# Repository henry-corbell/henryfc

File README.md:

# henryfc

server for tracking changes and updates for the HenryFC flight controller

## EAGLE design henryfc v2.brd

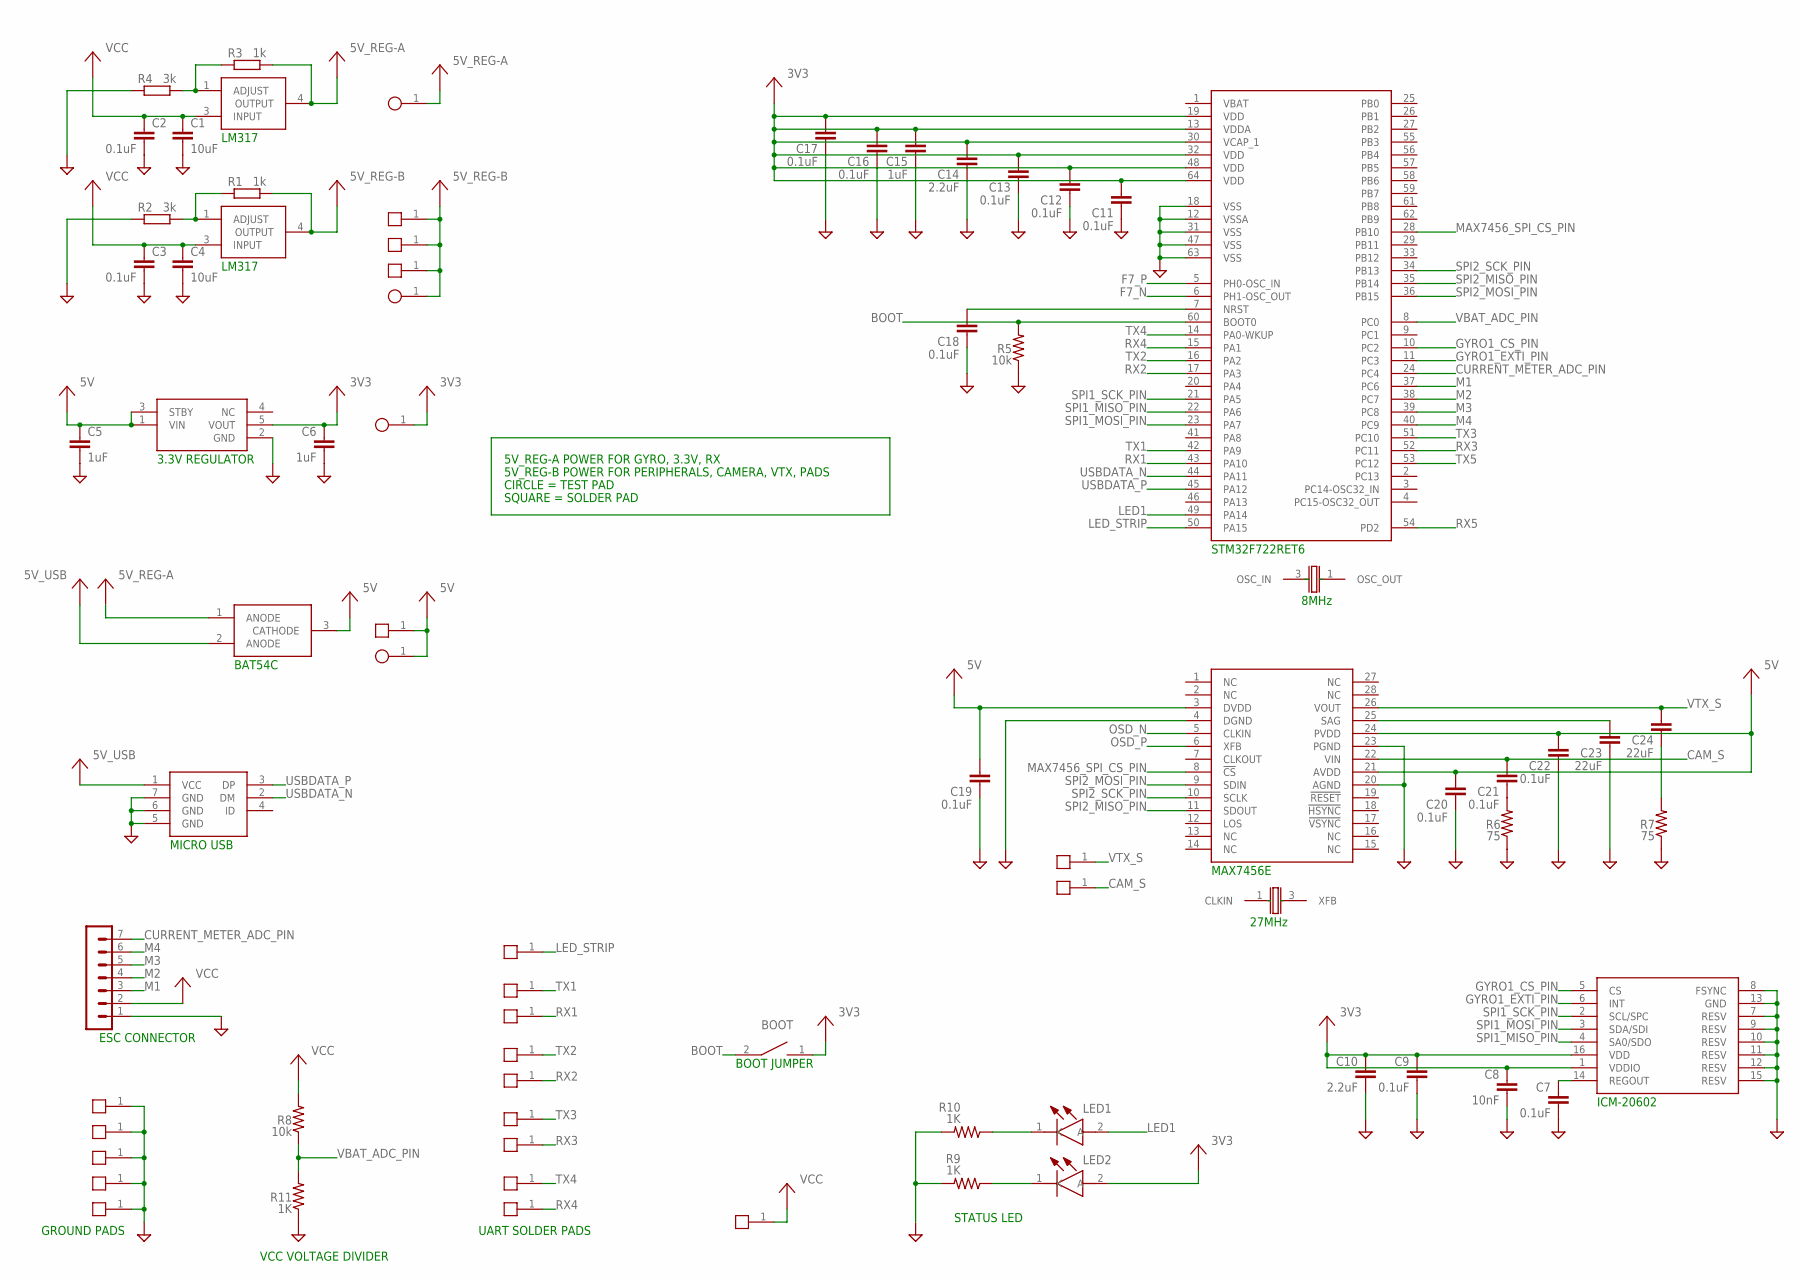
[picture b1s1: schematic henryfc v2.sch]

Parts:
C1, C4: 10uF; C0603
C2, C3: 0.1uF; C0603
C5, C6: 1uF; C0603
C7, C9, C11, C12, C13, C16, C17, C18, C19, C20, C21, C22: 0.1uF; C0402
C8: 10nF; C0402
C10, C14: 2.2uF; C0402
C15: 1uF; C0402
C23, C24: 22uF; C0402
LED1: KB_DELPS2.12-QHRI-24-Z555-10-S; KBDELPS212QHRI24Z55510S
LED2: KR_DELPS1.22-UHVI-26-H3Q4; KRDELPS122UHVI26H3Q4
R1, R3: 1k; R0603
R2, R4: 3k; R0603
R5, R8: 10k; R0402
R6, R7: 75; R0402
R9, R10, R11: 1K; R0402
TP1, TP2, TP3, TP4: TESTPOINT
U$1: BAT54C; SOT-23
U$2: BUXXSD5WG-3.3V-LDO; SSOP5
U$3, U$4: LM317DCYR; SOT-223
U$5: STM32F722; LQFP64
U$6: MICRO-USB
U$7: MAX7456; SSOP28
U$8: ICM-20602; LGA16-3X3
U$9: ECX-32-8MHZ; ECX-32-XTAL
U$10: NX3225GA-27MHZ; 3.2X2.5-XTAL
U$11: BOOT_JUMPER
U$13, U$14, U$15, U$19, U$20, U$21, U$22, U$23, U$24, U$25, U$26, U$27, U$28, U$29, U$30, U$31, U$32, U$33, U$34, U$35, U$36: SOLDERPAD
X1: SM07B-SRSS-TB

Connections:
3V3: C6.1, C8.1, C9.1, C10.1, C11.1, C12.1, C13.1, C14.1, C15.1, C16.1, C17.1, LED2.2 (A), TP2.1, U$2.5 (VOUT), U$5.13 (VDDA), U$5.19 (VDD), U$5.30 (VCAP_1), U$5.32 (VDD), U$5.48 (VDD), U$5.64 (VDD), U$8.1 (VDDIO), U$8.16 (VDD), U$11.1 ()
5V: C5.1, C19.1, C20.1, C22.1, TP1.1, U$1.3 (CATHODE), U$2.1 (VIN), U$2.3 (STBY), U$7.3 (DVDD), U$7.21 (AVDD), U$7.24 (PVDD), U$15.1
5V_REG-A: R3.2, TP4.1, U$1.1 (ANODE), U$4.4 (OUTPUT)
5V_REG-B: R1.2, TP3.1, U$3.4 (OUTPUT), U$13.1, U$14.1, U$25.1
5V_USB: U$1.2 (ANODE), U$6.1 (VCC)
BOOT: R5.2, U$5.60 (BOOT0), U$11.2 ()
CAM_S: C21.1, U$7.22 (VIN), U$31.1
CURRENT_METER_ADC_PIN: U$5.24 (PC4), X1.7
F7_N: U$5.6 (PH1-OSC_OUT), U$9.1 (OSC_OUT)
F7_P: U$5.5 (PH0-OSC_IN), U$9.3 (OSC_IN)
GND: C1.2, C2.2, C3.2, C4.2, C5.2, C6.2, C7.2, C8.2, C9.2, C10.2, C11.2, C12.2, C13.2, C14.2, C15.2, C16.2, C17.2, C18.2, C19.2, C20.2, C22.2, C23.2, R2.1, R4.1, R5.1, R6.1, R7.1, R9.2, R10.2, R11.1, U$2.2 (GND), U$5.12 (VSSA), U$5.18 (VSS), U$5.31 (VSS), U$5.47 (VSS), U$5.63 (VSS), U$6.5 (GND), U$6.6 (GND), U$6.7 (GND), U$7.4 (DGND), U$7.20 (AGND), U$7.23 (PGND), U$8.7 (RESV), U$8.8 (FSYNC), U$8.9 (RESV), U$8.10 (RESV), U$8.11 (RESV), U$8.12 (RESV), U$8.13 (GND), U$8.15 (RESV), U$19.1, U$20.1, U$21.1, U$27.1, U$35.1, X1.1
GYRO1_CS_PIN: U$5.10 (PC2), U$8.5 (CS)
GYRO1_EXTI_PIN: U$5.11 (PC3), U$8.6 (INT)
LED1: LED1.2 (A), U$5.49 (PA14)
LED_STRIP: U$5.50 (PA15), U$23.1
M1: U$5.37 (PC6), X1.3
M2: U$5.38 (PC7), X1.4
M3: U$5.39 (PC8), X1.5
M4: U$5.40 (PC9), X1.6
MAX7456_SPI_CS_PIN: U$5.28 (PB10), U$7.8 (!CS)
unnamed: R1.1, R2.2, U$3.1 (ADJUST)
unnamed: R3.1, R4.2, U$4.1 (ADJUST)
unnamed: C18.1, U$5.7 (NRST)
unnamed: C23.1, U$7.25 (SAG)
unnamed: C21.2, R6.2
unnamed: C7.1, U$8.14 (REGOUT)
unnamed: C24.2, R7.2
unnamed: LED1.1 (K), R10.1
unnamed: LED2.1 (K), R9.1
OSD_N: U$7.5 (CLKIN), U$10.1 (CLKIN)
OSD_P: U$7.6 (XFB), U$10.3 (XFB)
RX1: U$5.43 (PA10), U$34.1
RX2: U$5.17 (PA3), U$24.1
RX3: U$5.52 (PC11), U$28.1
RX4: U$5.15 (PA1), U$32.1
RX5: U$5.54 (PD2)
SPI1_MISO_PIN: U$5.22 (PA6), U$8.4 (SA0/SDO)
SPI1_MOSI_PIN: U$5.23 (PA7), U$8.3 (SDA/SDI)
SPI1_SCK_PIN: U$5.21 (PA5), U$8.2 (SCL/SPC)
SPI2_MISO_PIN: U$5.35 (PB14), U$7.11 (SDOUT)
SPI2_MOSI_PIN: U$5.36 (PB15), U$7.9 (SDIN)
SPI2_SCK_PIN: U$5.34 (PB13), U$7.10 (SCLK)
TX1: U$5.42 (PA9), U$36.1
TX2: U$5.16 (PA2), U$22.1
TX3: U$5.51 (PC10), U$26.1
TX4: U$5.14 (PA0-WKUP), U$30.1
TX5: U$5.53 (PC12)
USBDATA_N: U$5.44 (PA11), U$6.2 (DM)
USBDATA_P: U$5.45 (PA12), U$6.3 (DP)
VBAT_ADC_PIN: R8.1, R11.2, U$5.8 (PC0)
VCC: C1.1, C2.1, C3.1, C4.1, R8.2, U$3.3 (INPUT), U$4.3 (INPUT), U$33.1, X1.2
VTX_S: C24.1, U$7.26 (VOUT), U$29.1

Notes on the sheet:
8MHz
ICM-20602
LM317
3.3V REGULATOR
BAT54C
MICRO USB
STM32F722RET6
27MHz
MAX7456E
ESC CONNECTOR
GROUND PADS
VCC VOLTAGE DIVIDER
UART SOLDER PADS
BOOT JUMPER
STATUS LED
5V_REG-A POWER FOR GYRO, 3.3V, RX
5V_REG-B POWER FOR PERIPHERALS, CAMERA, VTX, PADS
CIRCLE = TEST PAD
SQUARE = SOLDER PAD

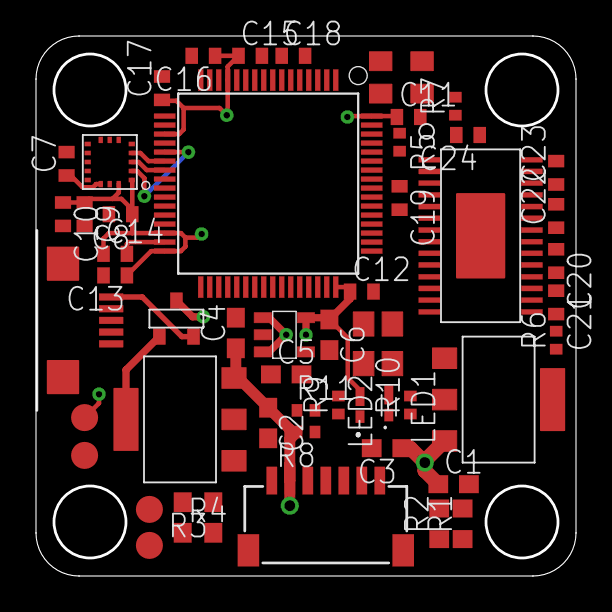
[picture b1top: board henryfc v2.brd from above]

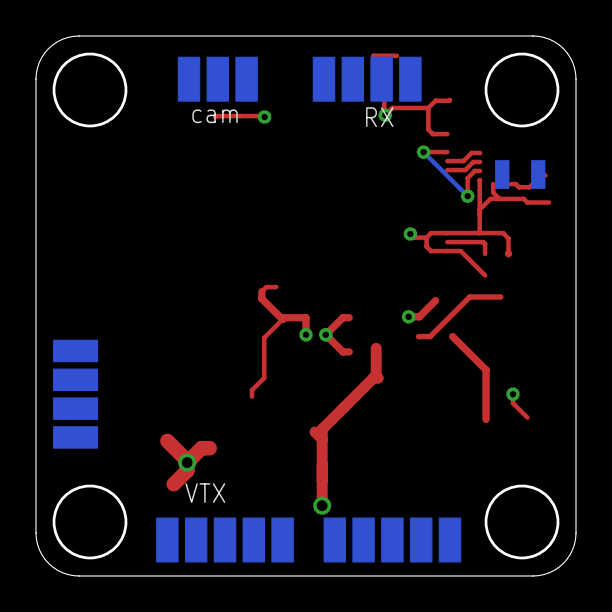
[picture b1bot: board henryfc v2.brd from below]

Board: 4 copper layers, 29.8 x 29.8 mm, 74 parts (22 on the bottom side), 50 nets.

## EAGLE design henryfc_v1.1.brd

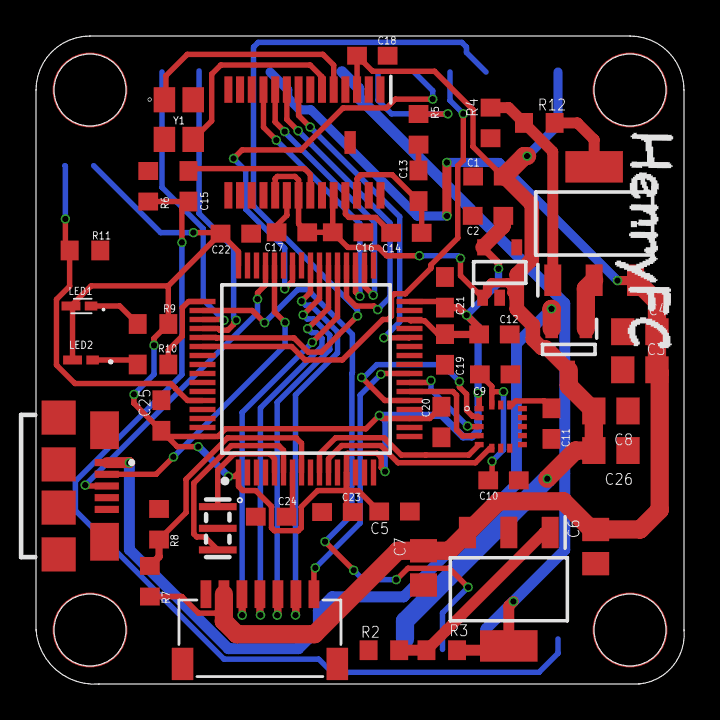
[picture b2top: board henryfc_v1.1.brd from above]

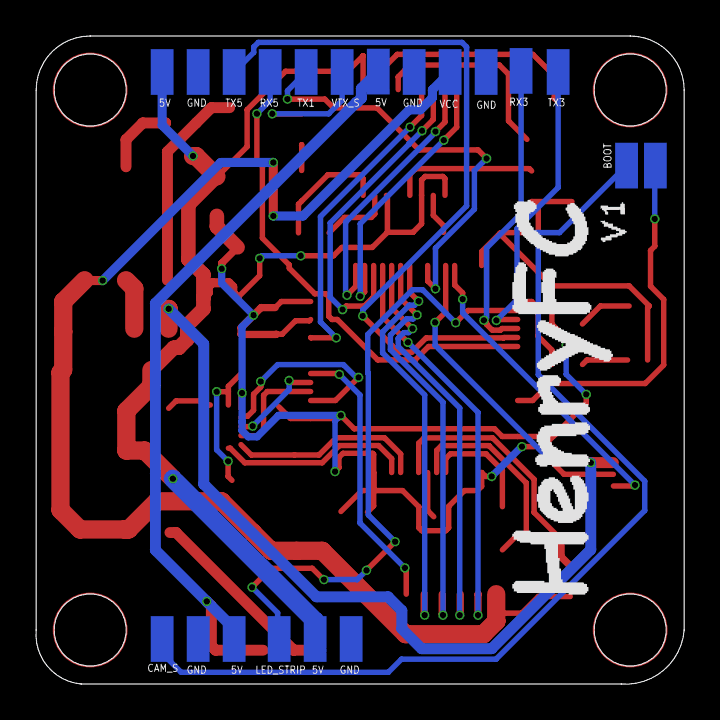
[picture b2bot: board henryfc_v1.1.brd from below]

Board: 2 copper layers, 36.0 x 36.0 mm, 70 parts (20 on the bottom side), 49 nets.

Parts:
C1, C2, C5: 1uF; C0603
C3, C6, C8: 0.1uF; C0805
C4, C7, C26: 10uF; C0805
C9, C11, C15, C16, C17, C18, C20, C21, C22, C23, C24, C25: 0.1uF; C0603
C10, C19: 2.2uF; C0603
C12: 10nF; C0603
C13, C14: 22uF; C0603
D1: BAT54C; SOT95P240X120-3N
IC1, IC5: LM317DCYR; SOT230P700X180-4N
IC2: ICM-20602; PULL-BACK-QFN-16
IC3: AT7456E; SOP65P640X120-29N
IC4: STM32F722RET6TR; QFP50P1200X1200X160-64N
J2: 10118192-0001LF; 101181920001LF
LED1: KB_DELPS2.12-QHRI-24-Z555-10-S; KBDELPS212QHRI24Z55510S
LED2: KR_DELPS1.22-UHVI-26-H3Q4; KRDELPS122UHVI26H3Q4
PAD1: CAM_S; SMD1,27-2,54
PAD2: VTX_S; SMD1,27-2,54
PAD3: BOOT; SMD1,27-2,54
PAD4: RX5; SMD1,27-2,54
PAD5: TX5; SMD1,27-2,54
PAD6: RX3; SMD1,27-2,54
PAD7: TX3; SMD1,27-2,54
PAD8: LED_STRIP; SMD1,27-2,54
PAD9, PAD16, PAD25, PAD26, PAD27: GND; SMD1,27-2,54
PAD11: TX1; SMD1,27-2,54
PAD18, PAD19, PAD20, PAD28: 5V; SMD1,27-2,54
PAD21: VCC; SMD1,27-2,54
PAD22: 3.3V; SMD1,27-2,54
PS1: BU33SD5WG-TR; SOT95P280X125-5N
R1: CSTCE8M00G55-R0; CSTCE12M0G55-R0
R2, R4: 3k; R0603
R3, R8, R9, R10, R12: 1k; R0603
R5, R6: 75R; R0603
R7: 10k; R0603
R11: 10K; R0603
X1: SM07B-SRSS-TB
Y1: NX3225GA-27.000M-STD-CRG-1; NX3225GA

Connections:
3.3V_REG: C2.1, C5.1, C12.2, C19.1, C20.1, C21.1, C22.1, C23.1, C25.1, IC2.1, IC4.1, IC4.13, IC4.19, IC4.30, IC4.32, IC4.48, IC4.64, LED1.2, LED2.2, PAD22.1, PS1.5, R9.1
5V_REG: D1.1, IC1.2, IC1.4, R12.2
5V_REG1: IC5.2, IC5.4, PAD19.1, PAD20.1, R3.2
5V_USB: D1.2, J2.1
+5V: C1.1, C8.2, C16.1, C17.1, C18.2, C26.2, D1.3, IC3.3, IC3.19, IC3.21, IC3.24, PAD18.1, PAD28.1, PS1.1, PS1.3
BOOT: IC4.60, PAD3.1, R11.1
CAM_S: C15.2, PAD1.1, R6.2
CURRENT_METER_ADC_PIN: IC4.24, X1.7
GND: C1.2, C2.2, C3.1, C4.1, C5.2, C6.1, C7.1, C8.1, C9.2, C10.2, C11.1, C12.1, C16.2, C17.2, C18.1, C19.2, C20.2, C21.2, C22.2, C23.2, C24.1, C25.2, C26.1, IC2.8, IC2.9, IC2.10, IC2.11, IC2.12, IC2.13, IC2.15, IC3.4, IC3.20, IC3.23, IC4.12, IC4.18, IC4.31, IC4.47, IC4.63, J2.5, PAD9.1, PAD16.1, PAD25.1, PAD26.1, PAD27.1, PS1.2, R1.2, R2.1, R4.1, R6.1, R8.1, R11.2, X1.1, Y1.2
GYRO_1_CS_PIN: IC2.5, IC4.10
GYRO_1_EXTI_PIN: IC2.6, IC4.11
LED1: IC4.49, R10.1
LED_STRIP: IC4.50, PAD8.1
M1: IC4.37, X1.3
M2: IC4.38, X1.4
M3: IC4.39, X1.5
M4: IC4.40, X1.6
MAX7456_SPI_CS_PIN: IC3.8, IC4.28
unnamed: IC5.1, R2.2, R3.1
unnamed: IC1.1, R4.2, R12.1
unnamed: C9.1, C10.1, IC2.16
unnamed: C11.2, IC2.14
unnamed: C14.1, IC3.25
unnamed: C13.1, C14.2, IC3.26
unnamed: C13.2, R5.1
unnamed: IC3.6, Y1.3
unnamed: C15.1, IC3.22
unnamed: IC3.5, Y1.1
unnamed: LED1.1, R9.2
unnamed: LED2.1, R10.2
NRST: C24.2, IC4.7
OSC_IN: IC4.5, R1.1
OSC_OUT: IC4.6, R1.3
OTG_FS_DM: IC4.44, J2.2
OTG_FS_DP: IC4.45, J2.3
RX3: IC4.52, PAD6.1
RX5: IC4.54, PAD4.1
SPI1_MISO_PIN: IC2.4, IC4.22
SPI1_MOSI_PIN: IC2.3, IC4.23
SPI1_SCK_PIN: IC2.2, IC4.21
SPI2_MISO_PIN: IC3.11, IC4.35
SPI2_MOSI_PIN: IC3.9, IC4.36
SPI2_SCK_PIN: IC3.10, IC4.34
TX1: IC4.42, PAD11.1
TX3: IC4.51, PAD7.1
TX5: IC4.53, PAD5.1
VBAT_ADC_PIN: IC4.8, R7.1, R8.2
VCC: C3.2, C4.2, C6.2, C7.2, IC1.3, IC5.3, PAD21.1, R7.2, X1.2
VTX_S: PAD2.1, R5.2

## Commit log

2020-09-08 first upload
2020-09-10 update 5v reg
2020-09-10 edit bypass caps
2020-09-15 update PCB layout
2020-09-16 update schematic
2020-09-20 MORE SCHEMATIC REVISION
2020-09-21 finalized v1.2 PCB layout
2020-09-29 finalized PCB
2020-10-21 cleaned files
2020-10-21 update files
2020-10-21 updated tplace logo
2020-12-22 start v2
    started creating custom symbols for cleaner schematic
2020-12-23 more schematic work
    updating for cleanliness & readability
2020-12-23 updated power, gyro for cleanliness & readability
2020-12-23 more schematic update
2020-12-27 FINALIZE SCHEMATIC V2
    much clean
2020-12-27 cleaned up
2020-12-27 upload library backup
2020-12-28 upload v2 PDF
2020-12-28 cleaning up schematic
2020-12-29 initial board layout
2021-01-04 updating pcb
2021-01-10 updated pcb
2021-03-11 more pcb work
